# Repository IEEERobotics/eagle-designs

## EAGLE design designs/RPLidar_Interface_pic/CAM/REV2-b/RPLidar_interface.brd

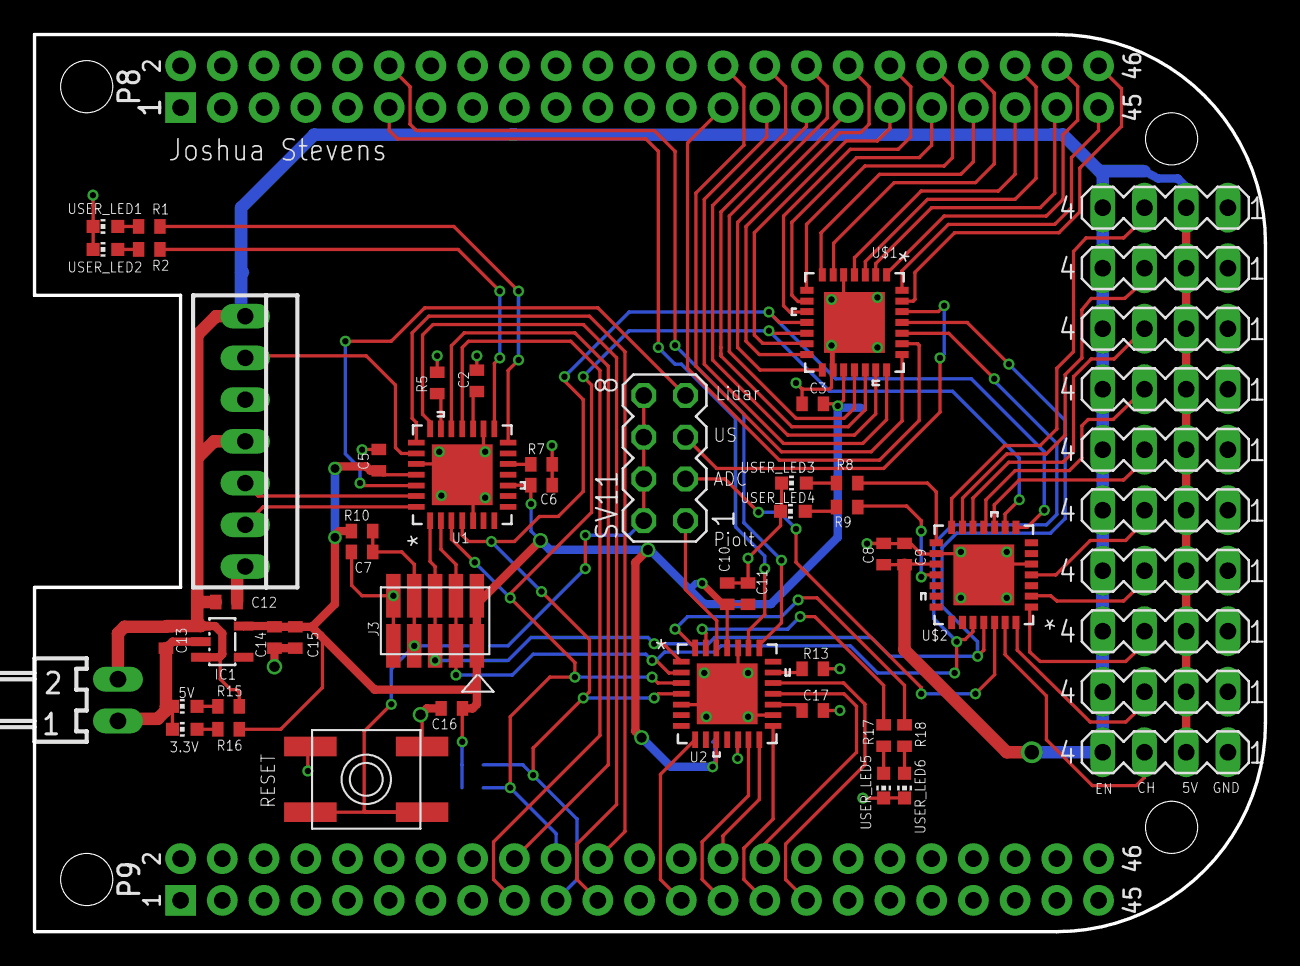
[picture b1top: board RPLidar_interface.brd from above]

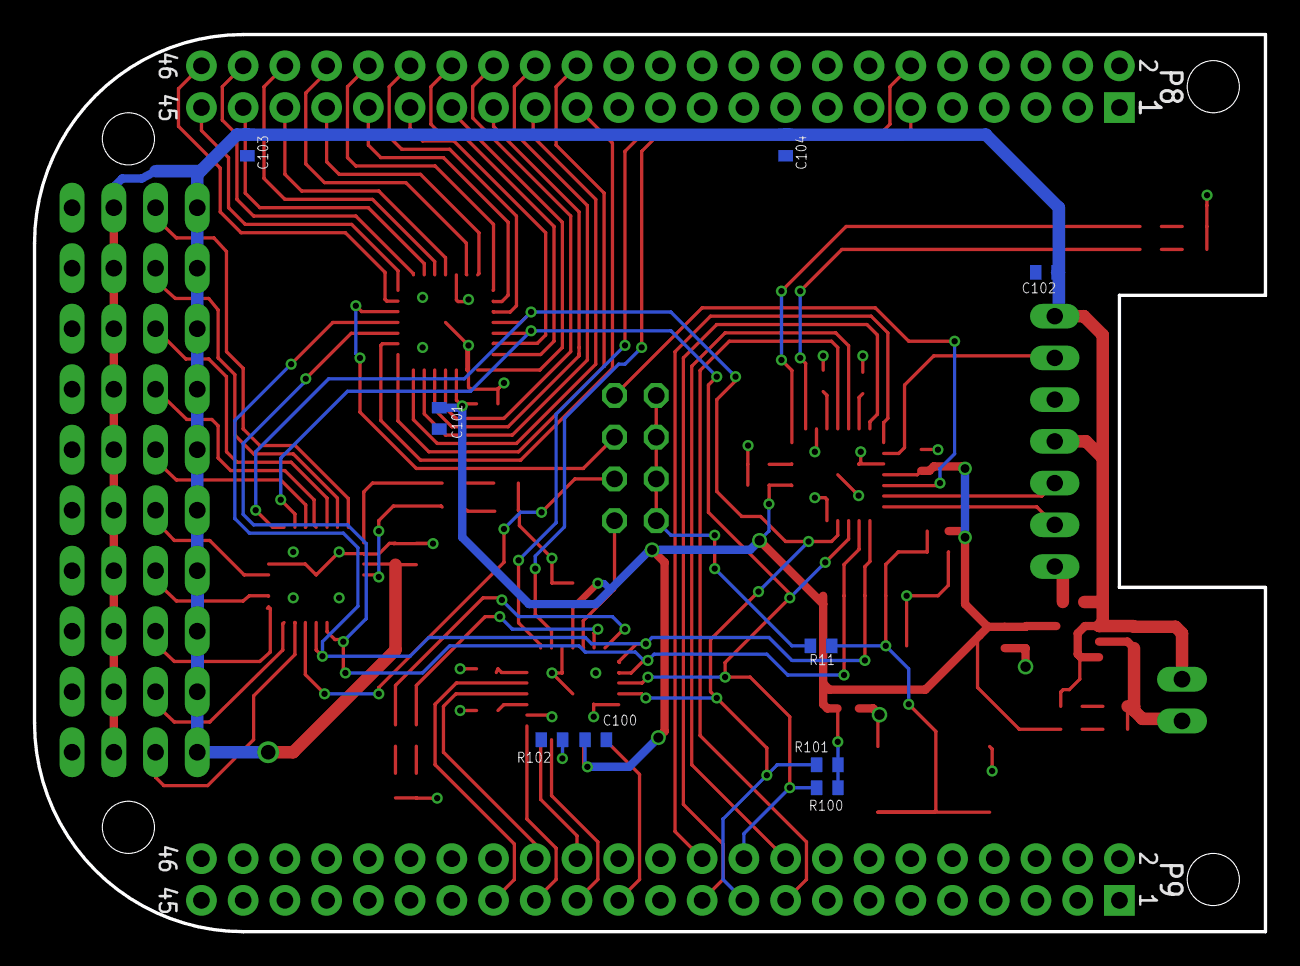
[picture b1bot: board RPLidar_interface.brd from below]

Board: 2 copper layers, 74.9 x 54.6 mm, 65 parts (9 on the bottom side), 78 nets.

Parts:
3.3V, 5V: CHIP-LED0603
C2, C7, C17: .1uF; C0402
C3, C6, C9, C10, C15, C100, C101: 0.1uF; C0402
C5, C8, C14: 1uF; C0402
C11, C16: .01uF; C0402
C12, C102, C103, C104: 5uF; C0402
C13: 10uF; C0402
IC1: TS5205; SOT25
J3: PIN-CONNECTOR74089; 10-PIN-SMD
J4: 22-05-7028-02; 7395-02
R1: 300; R0402
R2, R17, R18: 330; R0402
R5, R7, R13, R100, R101, R102: 0; R0402
R8, R9: 500; R0402
R10: 10k; R0402
R11: 100; R0402
R15, R16: 1K; R0402
RESET: EVQQ2; EVQ-Q2
SV1, SV2, SV3, SV4, SV5, SV6, SV7, SV8, SV9, SV10: MA04-1
SV11: MA04-2
U1, U2: PIC24FJ32GB002-I/ML; QFN65P600X600X100-29N
U$1, U$2: PIC16F73-I/ML; QFN65P600X600X100-28N
U$3: BEAGLE_BONE_BLACK_CAPE
USER_LED1, USER_LED2, USER_LED3, USER_LED4, USER_LED5, USER_LED6: CHIP-LED0603
X1: 22-23-2071

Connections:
5V: C8.1, C9.1, C12.1, C13.1, C102.1, C103.1, C104.1, IC1.1, IC1.3, J4.2, R15.2, SV1.2, SV1.4, SV2.2, SV2.4, SV3.2, SV3.4, SV4.2, SV4.4, SV5.2, SV5.4, SV6.2, SV6.4, SV7.2, SV7.4, SV8.2, SV8.4, SV9.2, SV9.4, SV10.2, SV10.4, U$2.17, X1.1, X1.4
!SS: U1.18, U$3.P9.17
+3V3: C3.1, C5.1, C6.1, C10.1, C11.1, C14.1, C15.1, C16.1, C100.1, C101.1, IC1.5, J3.1, J3.2, R10.2, R16.2, R100.1, R101.1, U1.10, U1.25, U2.10, U2.25, U$1.17
CH1: SV10.3, U$2.27
CH2: SV9.3, U$2.28
CH3: SV8.3, U$2.1
CH4: SV7.3, U$2.2
CH5: SV6.3, U$2.4
CH6: SV5.3, U$2.10
CH7: SV4.3, U$2.11
CH8: SV3.3, U$2.12
CH9: SV2.3, U$2.13
CH10: SV1.3, U$2.14
GND: 3.3V.C, 5V.C, C2.2, C3.2, C5.2, C6.2, C7.2, C8.2, C9.2, C10.2, C11.2, C12.2, C13.2, C14.2, C15.2, C16.2, C17.2, C100.2, C101.2, C102.2, C103.2, C104.2, IC1.2, J3.9, J3.10, J4.1, R5.2, R7.2, R13.2, R102.2, RESET.A, RESET.A', SV1.1, SV2.1, SV3.1, SV4.1, SV5.1, SV6.1, SV7.1, SV8.1, SV9.1, SV10.1, U1.5, U1.16, U1.24, U1.29, U2.5, U2.16, U2.24, U2.29, U$1.5, U$1.16, U$1.29, U$2.5, U$2.16, U$2.29, U$3.P8.1, U$3.P8.2, U$3.P9.1, U$3.P9.2, USER_LED1.C, USER_LED2.C, USER_LED3.C, USER_LED4.C, USER_LED5.C, USER_LED6.C, X1.3, X1.7
ICSPCLK: J3.3, J3.4, U1.2, U2.2, U$1.24, U$2.24
ICSPDAT: J3.5, J3.6, U1.1, U2.1, U$1.25, U$2.25
MCLR/VPP_A: SV11.3, U$2.26
MCLR/VPP_P: SV11.1, U2.26
MCLR/VPP_U: SV11.5, U$1.26
MCLR_LIDAR: C7.1, J3.7, J3.8, R10.1, R11.2, RESET.B, RESET.B'
MISO: U1.21, U$3.P9.21
MOSI: U1.19, U$3.P9.18
unnamed: 3.3V.A, R16.1
unnamed: R1.1, USER_LED1.A
unnamed: R2.1, USER_LED2.A
unnamed: 5V.A, R15.1
unnamed: R17.1, USER_LED5.A
unnamed: R18.1, USER_LED6.A
unnamed: R8.1, USER_LED3.A
unnamed: R9.1, USER_LED4.A
unnamed: R11.1, SV11.2, SV11.4, SV11.6, SV11.8
P8.11: U2.23, U$3.P8.11
P8.12: U2.22, U$3.P8.12
P8.27: U$1.23, U$3.P8.27
P8.28: U$1.22, U$3.P8.28
P8.29: U$1.21, U$3.P8.29
P8.30: U$1.20, U$3.P8.30
P8.31: U$1.19, U$3.P8.31
P8.32: U$1.18, U$3.P8.32
P8.33: U$1.15, U$3.P8.33
P8.34: U$1.14, U$3.P8.34
P8.35: U$1.13, U$3.P8.35
P8.36: U$1.10, U$3.P8.36
P8.37: U$1.9, U$3.P8.37
P8.38: U$1.8, U$3.P8.38
P8.39: U$1.7, U$3.P8.39
P8.40: U$1.6, U$3.P8.40
P8.41: U$1.4, U$3.P8.41
P8.42: U$1.3, U$3.P8.42
P8.43: U$1.2, U$3.P8.43
P8.44: U$1.1, U$3.P8.44
P8.45: U$1.28, U$3.P8.45
P8.46: U$1.27, U$3.P8.46
P9.25: U2.8, U$3.P9.25
P9.27: U2.13, U$3.P9.27
P9.28: U2.14, U$3.P9.28
P9.29: U2.15, U$3.P9.29
P9.30: U2.18, U$3.P9.30
P9.31: U2.19, U$3.P9.31
RPLIDAR_EN: U1.23, X1.2
SCL: R101.2, U1.4, U2.4, U$1.11, U$2.8, U$3.P9.19
SCLK: U1.22, U$3.P9.22
SDA: R100.2, U1.3, U2.3, U$1.12, U$2.9, U$3.P9.20
UART_RX: U1.27, X1.5
UART_TX: U1.28, X1.6
USER1: R1.2, U1.14
USER2: R2.2, U1.15
USER3: R18.2, U2.28
USER4: R17.2, U2.27
USER5: R8.2, U$2.15
USER6: R9.2, U$2.18
VBUS: R7.1, U1.12
VBUS_P: R102.1, U2.12
VDDCORE: C2.1, U1.17
VDDCORE_P: C17.1, U2.17
VPP/MCLR: SV11.7, U1.26
VUSB: R5.1, U1.20
VUSB_P: R13.1, U2.20

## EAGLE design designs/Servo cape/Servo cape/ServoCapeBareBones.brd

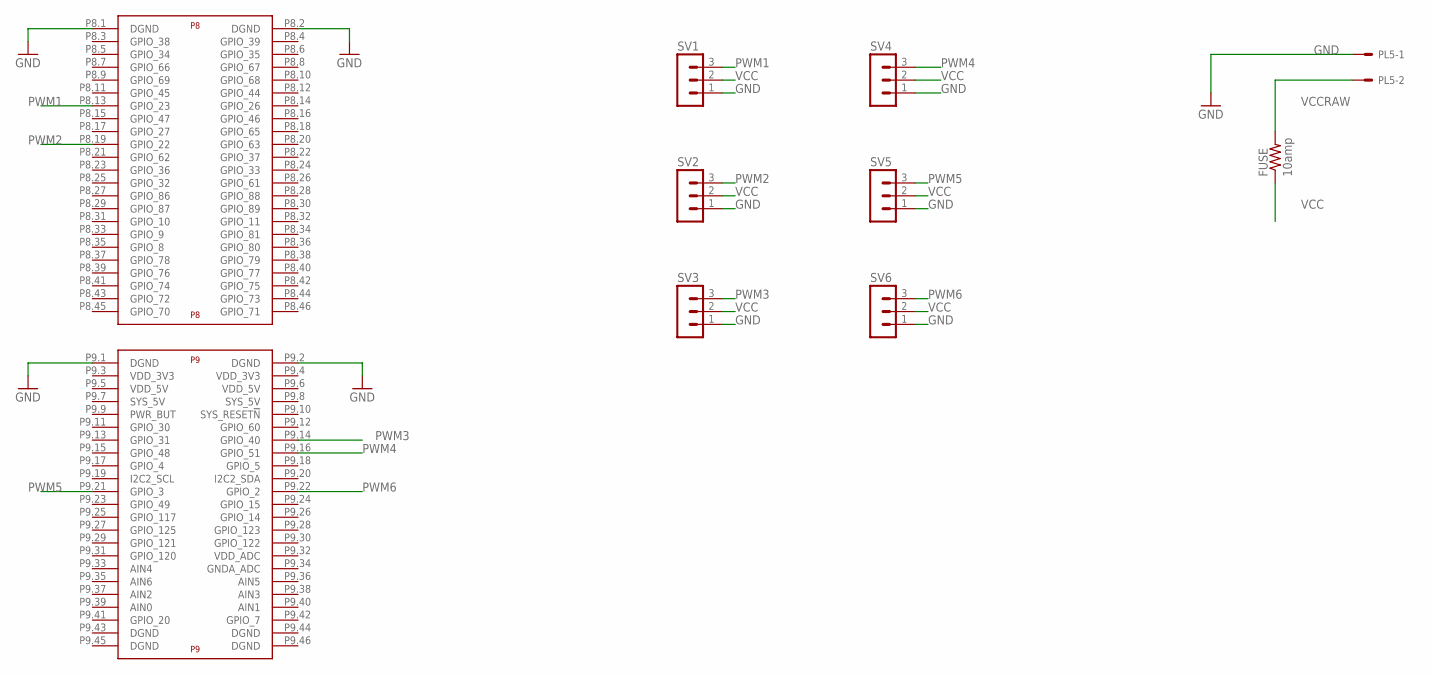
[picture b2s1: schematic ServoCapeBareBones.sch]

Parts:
FUSE: 10amp; R1206
PL5: 555X-2H; 5569-2
SV1, SV2, SV3, SV4, SV5, SV6: MA03-1
U$1: BEAGLE_BONE_BLACK_CAPE

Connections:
GND: PL5.1, SV1.1, SV2.1, SV3.1, SV4.1, SV5.1, SV6.1, U$1.P8.1 (DGND), U$1.P8.2 (DGND), U$1.P9.1 (DGND), U$1.P9.2 (DGND)
PWM1: SV1.3, U$1.P8.13 (GPIO_23)
PWM2: SV2.3, U$1.P8.19 (GPIO_22)
PWM3: SV3.3, U$1.P9.14 (GPIO_40)
PWM4: SV4.3, U$1.P9.16 (GPIO_51)
PWM5: SV5.3, U$1.P9.21 (GPIO_3)
PWM6: SV6.3, U$1.P9.22 (GPIO_2)
VCC: FUSE.1, SV1.2, SV2.2, SV3.2, SV4.2, SV5.2, SV6.2
VCCRAW: FUSE.2, PL5.2

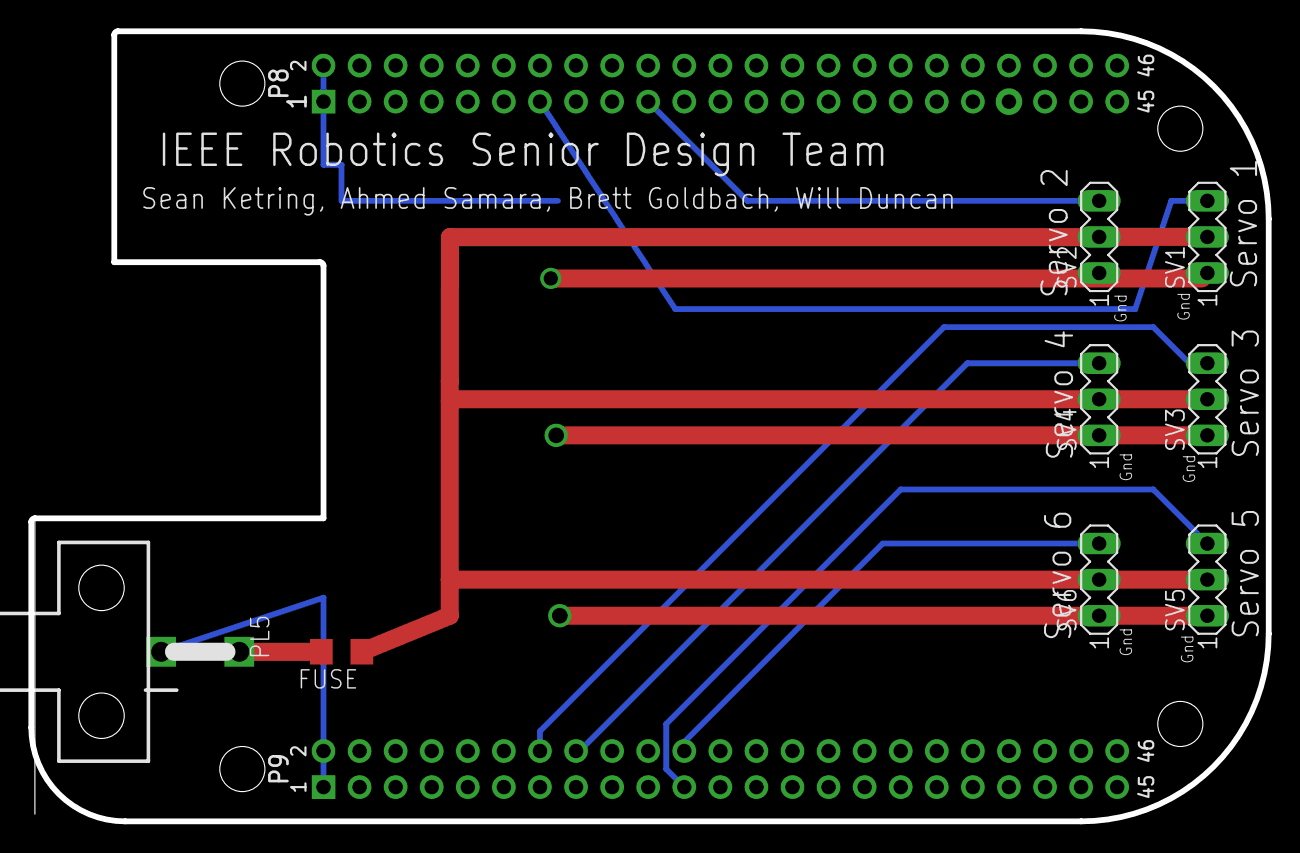
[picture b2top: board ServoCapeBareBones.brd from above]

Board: 2 copper layers, 87.1 x 55.6 mm, 9 parts (0 on the bottom side), 9 nets.

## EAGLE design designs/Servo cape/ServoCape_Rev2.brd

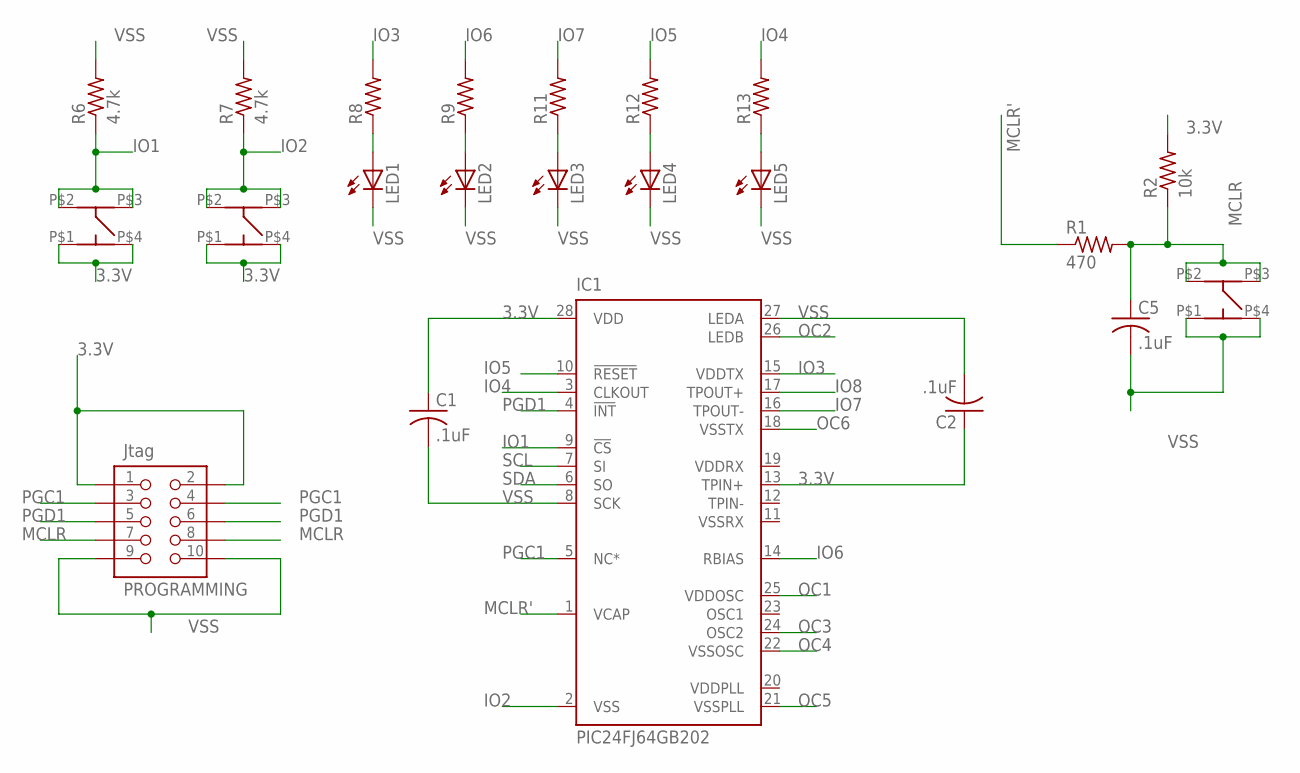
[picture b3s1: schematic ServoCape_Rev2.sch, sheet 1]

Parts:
C1, C2, C5: .1uF; C0805
IC1: PIC24FJ64GB202; DIL28-3
LED1, LED2, LED3, LED4, LED5: LED_LEDCHIPLED_1206; LED_CHIPLED_1206
PROGRAMMING: Jtag; MOTHER-BOARD-REV5_10-PIN-SMD
R1: 470; R0805
R2: 10k; R0805
R6, R7: 4.7k; R0805
R8, R9, R11, R12, R13: R-US_M0805; M0805
U$1: Switch3; MC32882_FINAL
U$4: Switch1; MC32882_FINAL
U$5: Switch2; MC32882_FINAL

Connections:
3.3V: C1.1, C2.1, IC1.13 (TPIN+), IC1.28 (VDD), PROGRAMMING.1, PROGRAMMING.2, R2.2, U$4.P$1 (P1), U$4.P$4 (P4), U$5.P$1 (P1), U$5.P$4 (P4); also elsewhere on the board
IO1: IC1.9 (!CS), R6.1, U$4.P$2 (P2), U$4.P$3 (P3)
IO2: IC1.2 (VSS), R7.1, U$5.P$2 (P2), U$5.P$3 (P3)
IO3: IC1.15 (VDDTX), R8.2
IO4: IC1.3 (CLKOUT), R13.2
IO5: IC1.10 (!RESET), R12.2
IO6: IC1.14 (RBIAS), R9.2
IO7: IC1.16 (TPOUT-), R11.2
IO8: IC1.17 (TPOUT+)
MCLR: C5.1, PROGRAMMING.7, PROGRAMMING.8, R1.2, R2.1, U$1.P$2 (P2), U$1.P$3 (P3)
MCLR': IC1.1 (VCAP), R1.1
unnamed: LED1.A, R8.1
unnamed: LED2.A, R9.1
unnamed: LED3.A, R11.1
unnamed: LED4.A, R12.1
unnamed: LED5.A, R13.1
OC1: IC1.25 (VDDOSC); also elsewhere on the board
OC2: IC1.26 (LEDB); also elsewhere on the board
OC3: IC1.24 (OSC2); also elsewhere on the board
OC4: IC1.22 (VSSOSC); also elsewhere on the board
OC5: IC1.21 (VSSPLL); also elsewhere on the board
OC6: IC1.18 (VSSTX); also elsewhere on the board
PGC1: IC1.5 (NC*), PROGRAMMING.3, PROGRAMMING.4
PGD1: IC1.4 (!INT), PROGRAMMING.5, PROGRAMMING.6
SCL: IC1.7 (SI); also elsewhere on the board
SDA: IC1.6 (SO); also elsewhere on the board
VSS: C1.2, C2.2, C5.2, IC1.8 (SCK), IC1.27 (LEDA), LED1.C, LED2.C, LED3.C, LED4.C, LED5.C, PROGRAMMING.9, PROGRAMMING.10, R6.2, R7.2, U$1.P$1 (P1), U$1.P$4 (P4); also elsewhere on the board

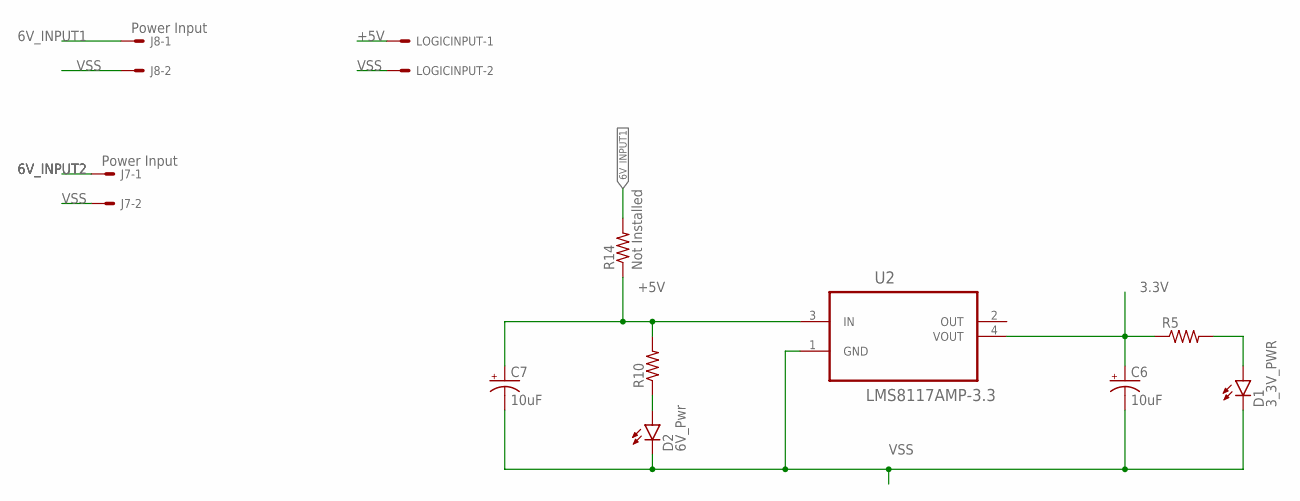
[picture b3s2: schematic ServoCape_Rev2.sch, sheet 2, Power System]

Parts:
C6, C7: 10uF; EIA3216
D1: 3_3V_PWR; FKIT-LED-1206
D2: 6V_Pwr; FKIT-LED-1206
J7, J8: Power Input; 7395-02
LOGICINPUT: 22-05-7028-02; 7395-02
R5, R10: R-US_R0805W; R0805W
R14: Not Installed; R0402
U2: LMS8117AMP-3.3; SOT230P696X180-4N

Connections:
3.3V: C6.A (+), R5.1, U2.4 (VOUT); also elsewhere on the board
6V_INPUT1: J8.1, R14.2; also elsewhere on the board
6V_INPUT2: J7.1; also elsewhere on the board
+5V: C7.A (+), LOGICINPUT.1, R10.2, R14.1, U2.3 (IN)
unnamed: D1.A, R5.2
unnamed: D2.A, R10.1
VSS: C6.C (-), C7.C (-), D1.C, D2.C, J7.2, J8.2, LOGICINPUT.2, U2.1 (GND); also elsewhere on the board

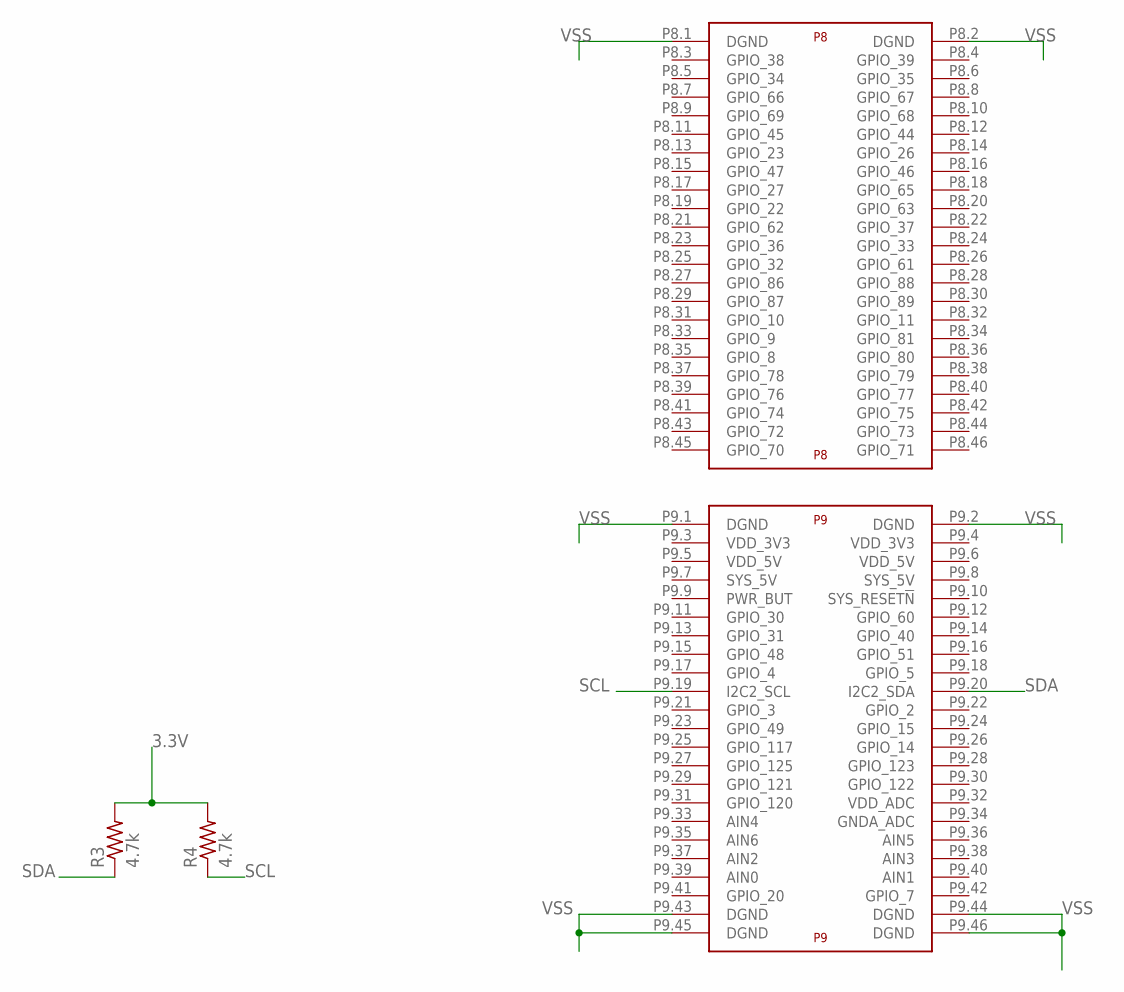
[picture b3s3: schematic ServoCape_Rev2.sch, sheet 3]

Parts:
R3, R4: 4.7k; R0805
U$2: BEAGLE_BONE_BLACK_CAPE

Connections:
3.3V: R3.2, R4.2; also elsewhere on the board
SCL: R4.1, U$2.P9.19 (I2C2_SCL); also elsewhere on the board
SDA: R3.1, U$2.P9.20 (I2C2_SDA); also elsewhere on the board
VSS: U$2.P8.1 (DGND), U$2.P8.2 (DGND), U$2.P9.1 (DGND), U$2.P9.2 (DGND), U$2.P9.43 (DGND), U$2.P9.44 (DGND), U$2.P9.45 (DGND), U$2.P9.46 (DGND); also elsewhere on the board

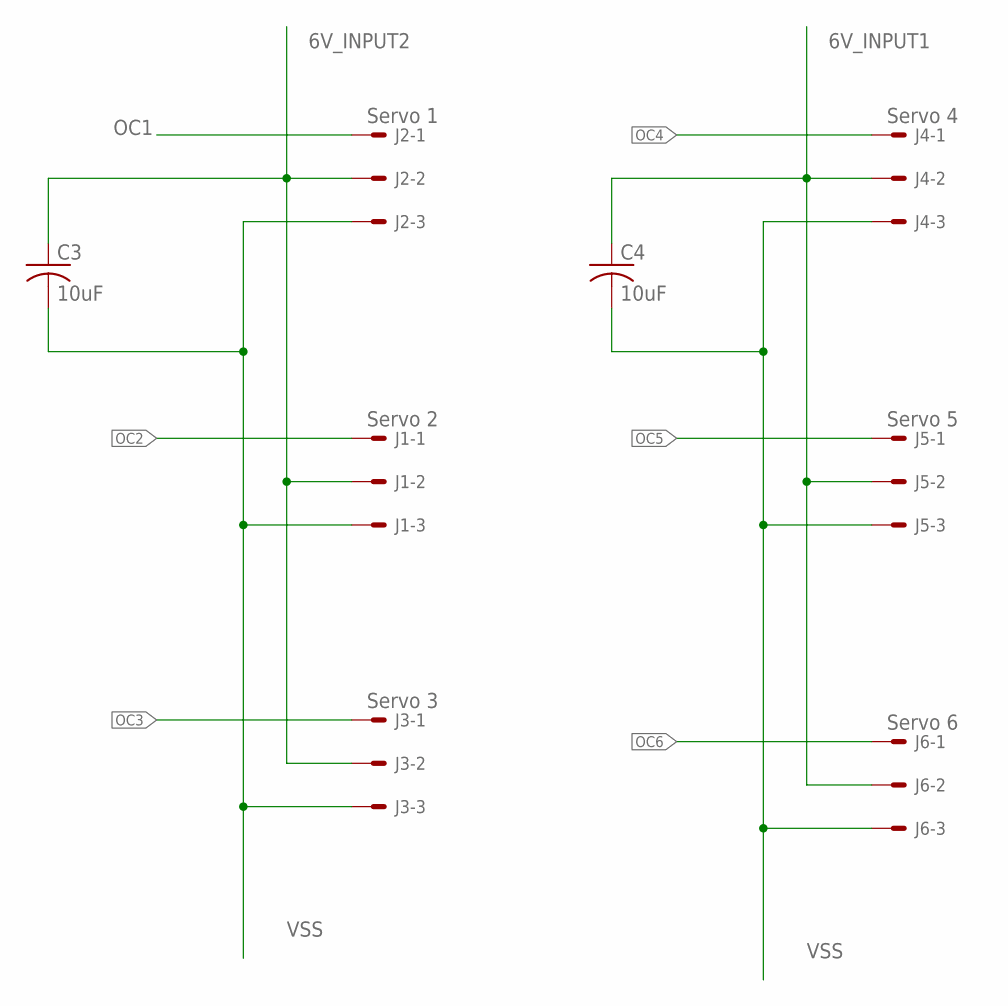
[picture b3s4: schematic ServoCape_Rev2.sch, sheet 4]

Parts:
C3, C4: 10uF; C0805
J1: Servo 2; 7395-03
J2: Servo 1; 7395-03
J3: Servo 3; 7395-03
J4: Servo 4; 7395-03
J5: Servo 5; 7395-03
J6: Servo 6; 7395-03

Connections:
6V_INPUT1: C4.1, J4.2, J5.2, J6.2; also elsewhere on the board
6V_INPUT2: C3.1, J1.2, J2.2, J3.2; also elsewhere on the board
OC1: J2.1; also elsewhere on the board
OC2: J1.1; also elsewhere on the board
OC3: J3.1; also elsewhere on the board
OC4: J4.1; also elsewhere on the board
OC5: J5.1; also elsewhere on the board
OC6: J6.1; also elsewhere on the board
VSS: C3.2, C4.2, J1.3, J2.3, J3.3, J4.3, J5.3, J6.3; also elsewhere on the board

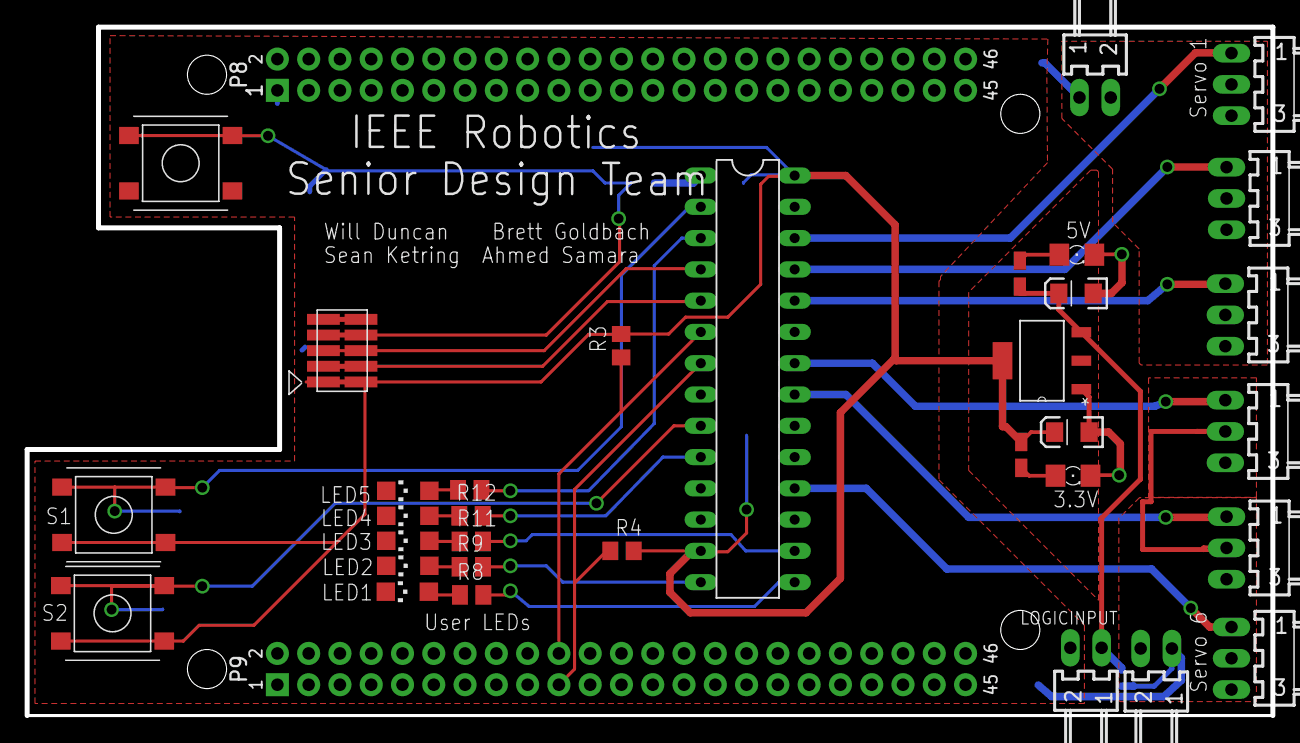
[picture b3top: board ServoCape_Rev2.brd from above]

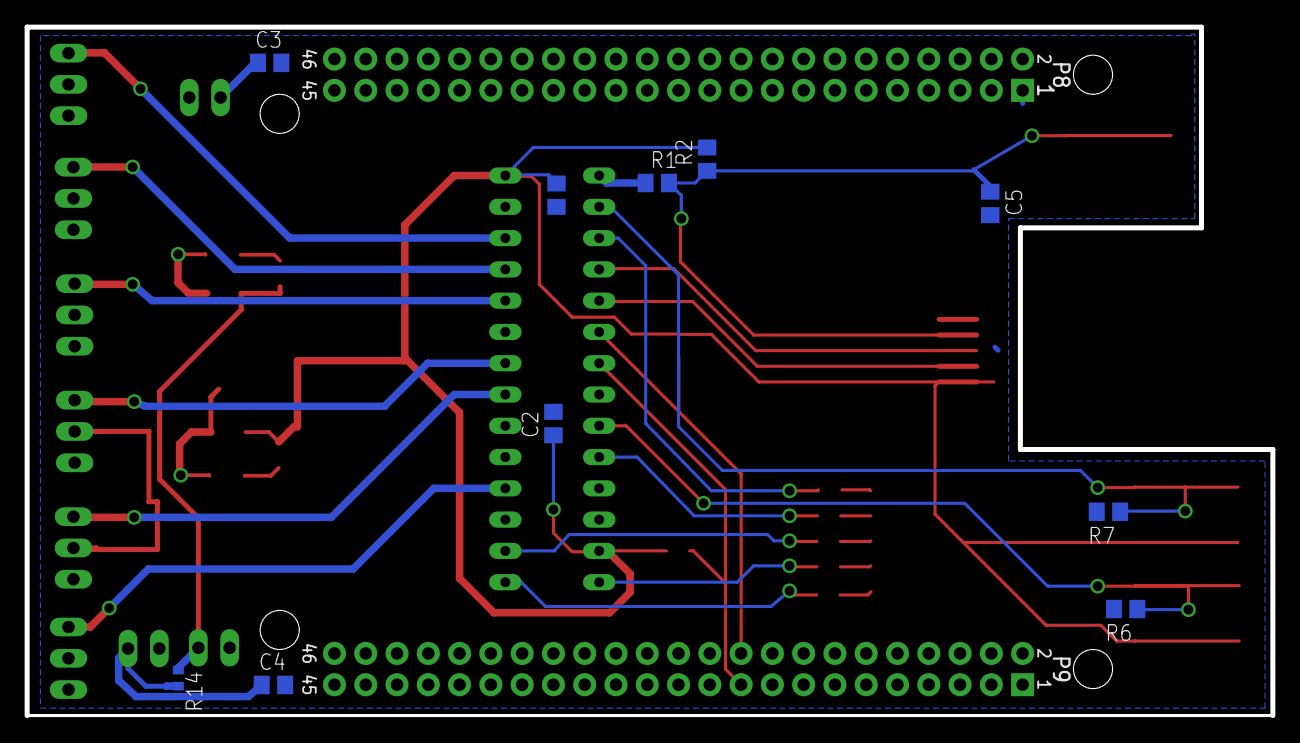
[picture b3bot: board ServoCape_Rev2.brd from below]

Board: 2 copper layers, 101.2 x 55.9 mm, 44 parts (10 on the bottom side), 31 nets.

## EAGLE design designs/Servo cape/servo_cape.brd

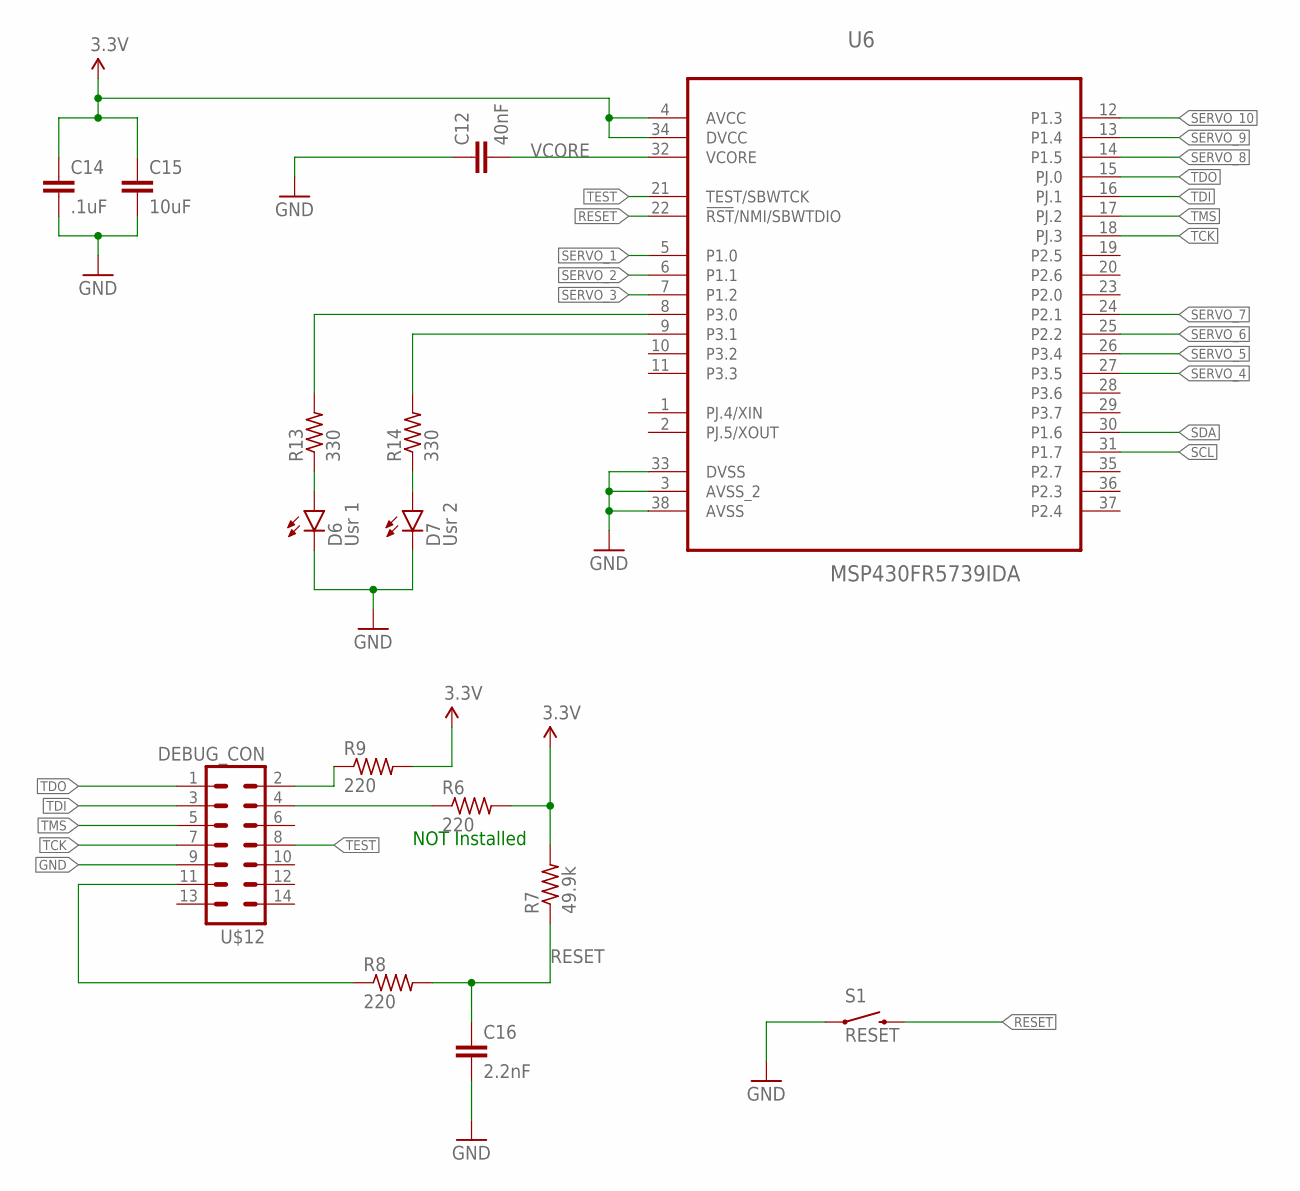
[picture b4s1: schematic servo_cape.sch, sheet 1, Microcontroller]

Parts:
C12: 40nF; 0805
C14: .1uF; 0805
C15: 10uF; 0805
C16: 2.2nF; 0805
D6: Usr 1; FKIT-LED-1206
D7: Usr 2; FKIT-LED-1206
R6, R8, R9: 220; R0805W
R7: 49.9k; R0805W
R13, R14: 330; R0805W
S1: RESET; TACTILE_SWITCH_TALL
U6: MSP430FR5739IDA; SOP65P810X120-38N
U$12: DEBUG_CON; DEBUG_SM

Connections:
3.3V: C14.1, C15.1, R6.2, R7.2, R9.2, U6.4 (AVCC), U6.34 (DVCC); also elsewhere on the board
GND: C12.1, C14.2, C15.2, C16.2, D6.C, D7.C, S1.A2 (1), U6.3 (AVSS_2), U6.33 (DVSS), U6.38 (AVSS), U$12.9; also elsewhere on the board
unnamed: R14.2, U6.9 (P3.1)
unnamed: R6.1, U$12.4
unnamed: D6.A, R13.1
unnamed: D7.A, R14.1
unnamed: R8.1, U$12.11
unnamed: R9.1, U$12.2
unnamed: R13.2, U6.8 (P3.0)
RESET: C16.1, R7.1, R8.2, S1.B2 (2), U6.22 (!RST!/NMI/SBWTDIO)
SCL: U6.31 (P1.7); also elsewhere on the board
SDA: U6.30 (P1.6); also elsewhere on the board
SERVO_1: U6.5 (P1.0); also elsewhere on the board
SERVO_2: U6.6 (P1.1); also elsewhere on the board
SERVO_3: U6.7 (P1.2); also elsewhere on the board
SERVO_4: U6.27 (P3.5); also elsewhere on the board
SERVO_5: U6.26 (P3.4); also elsewhere on the board
SERVO_6: U6.25 (P2.2); also elsewhere on the board
SERVO_7: U6.24 (P2.1); also elsewhere on the board
SERVO_8: U6.14 (P1.5)
SERVO_9: U6.13 (P1.4)
SERVO_10: U6.12 (P1.3)
TCK: U6.18 (PJ.3), U$12.7
TDI: U6.16 (PJ.1), U$12.3
TDO: U6.15 (PJ.0), U$12.1
TEST: U6.21 (TEST/SBWTCK), U$12.8
TMS: U6.17 (PJ.2), U$12.5
VCORE: C12.2, U6.32 (VCORE)

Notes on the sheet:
NOT Installed

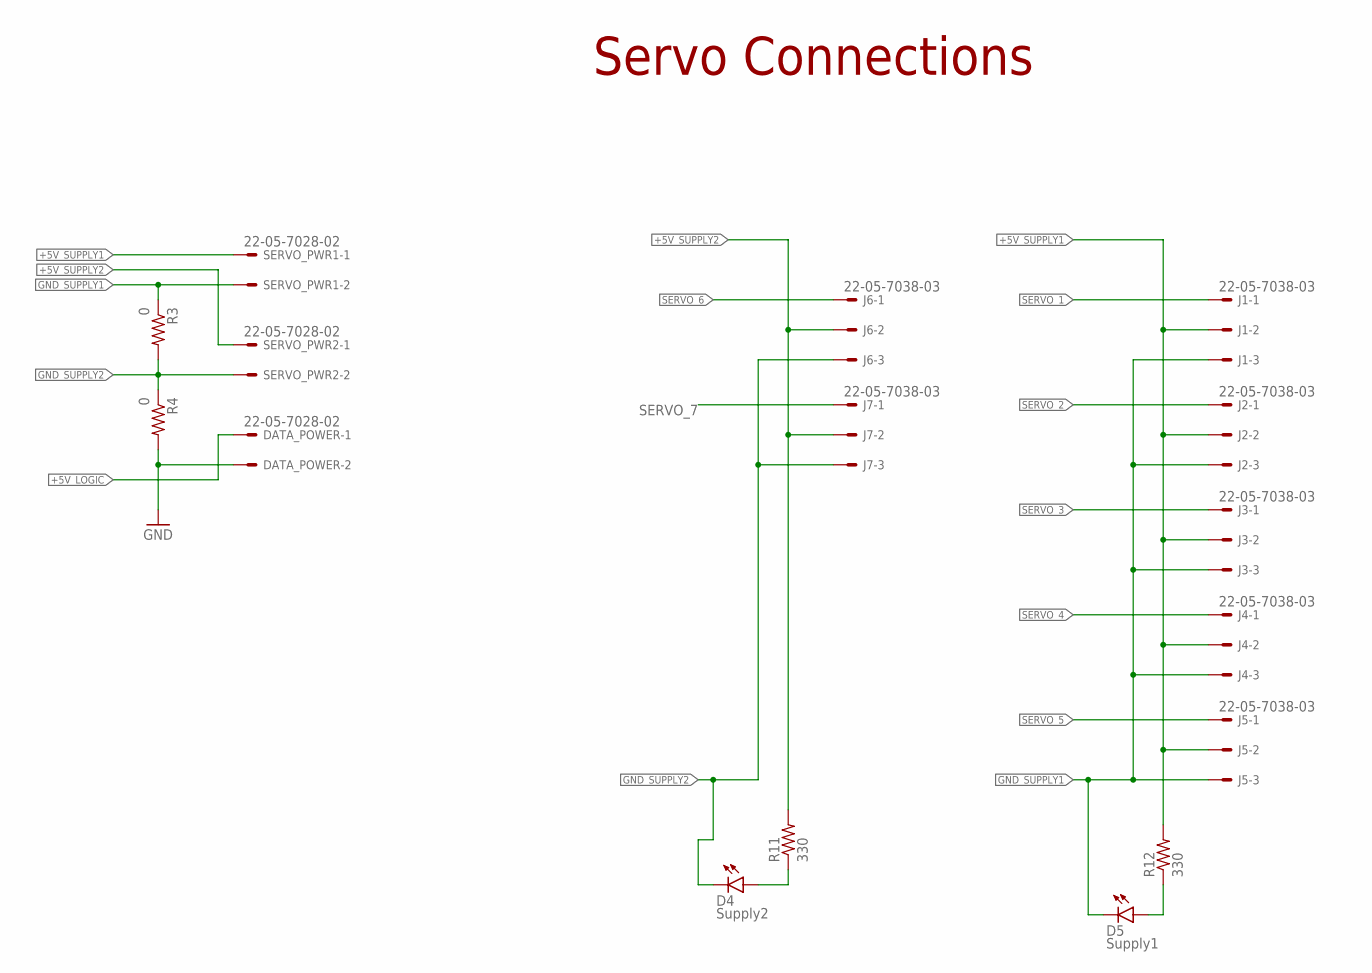
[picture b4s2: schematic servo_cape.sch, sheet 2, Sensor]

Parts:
D4: Supply2; FKIT-LED-1206
D5: Supply1; FKIT-LED-1206
DATA_POWER: 22-05-7028-02; 7395-02
J1, J2, J3, J4, J5, J6, J7: 22-05-7038-03; 7395-03
R3, R4: 0; R0805W
R11, R12: 330; R0805W
SERVO_PWR1, SERVO_PWR2: 22-05-7028-02; 7395-02

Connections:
+5V_LOGIC: DATA_POWER.1; also elsewhere on the board
+5V_SUPPLY1: J1.2, J2.2, J3.2, J4.2, J5.2, R12.2, SERVO_PWR1.1
+5V_SUPPLY2: J6.2, J7.2, R11.2, SERVO_PWR2.1
GND: DATA_POWER.2, R4.2; also elsewhere on the board
GND_SUPPLY1: D5.C, J1.3, J2.3, J3.3, J4.3, J5.3, R3.1, SERVO_PWR1.2
GND_SUPPLY2: D4.C, J6.3, J7.3, R3.2, R4.1, SERVO_PWR2.2
unnamed: D5.A, R12.1
unnamed: D4.A, R11.1
SERVO_1: J1.1; also elsewhere on the board
SERVO_2: J2.1; also elsewhere on the board
SERVO_3: J3.1; also elsewhere on the board
SERVO_4: J4.1; also elsewhere on the board
SERVO_5: J5.1; also elsewhere on the board
SERVO_6: J6.1; also elsewhere on the board
SERVO_7: J7.1; also elsewhere on the board

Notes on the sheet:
Servo Connections

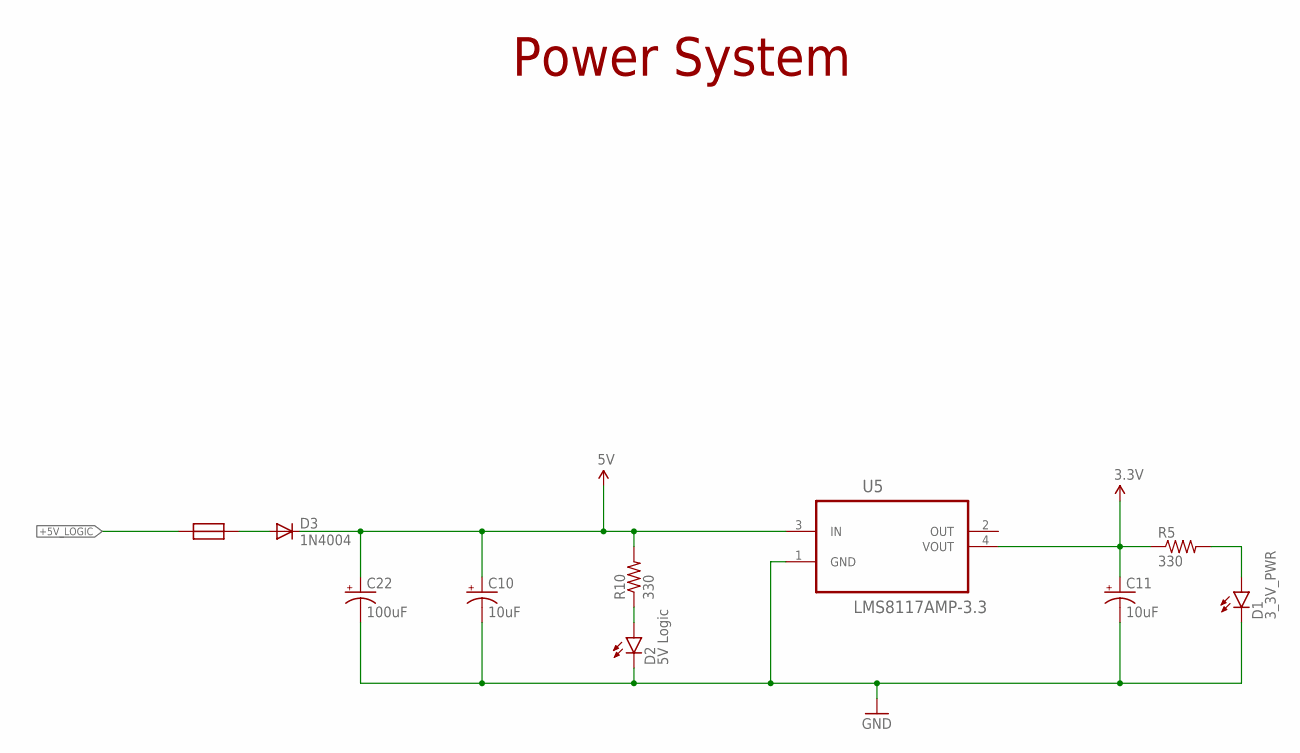
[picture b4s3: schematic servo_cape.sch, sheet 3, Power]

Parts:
C10, C11: 10uF; EIA3216
C22: 100uF; EIA7343
D1: 3_3V_PWR; FKIT-LED-1206
D2: 5V Logic; FKIT-LED-1206
D3: 1N4004; DO41-10
R5, R10: 330; R0805W
U5: LMS8117AMP-3.3; SOT230P696X180-4N
U$3: NANO_FUSE

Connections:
3.3V: C11.A (+), R5.1, U5.4 (VOUT); also elsewhere on the board
5V: C10.A (+), C22.A (+), D3.C, R10.2, U5.3 (IN)
+5V_LOGIC: U$3.1; also elsewhere on the board
GND: C10.C (-), C11.C (-), C22.C (-), D1.C, D2.C, U5.1 (GND); also elsewhere on the board
unnamed: D1.A, R5.2
unnamed: D2.A, R10.1
unnamed: D3.A, U$3.2

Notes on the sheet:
Power System

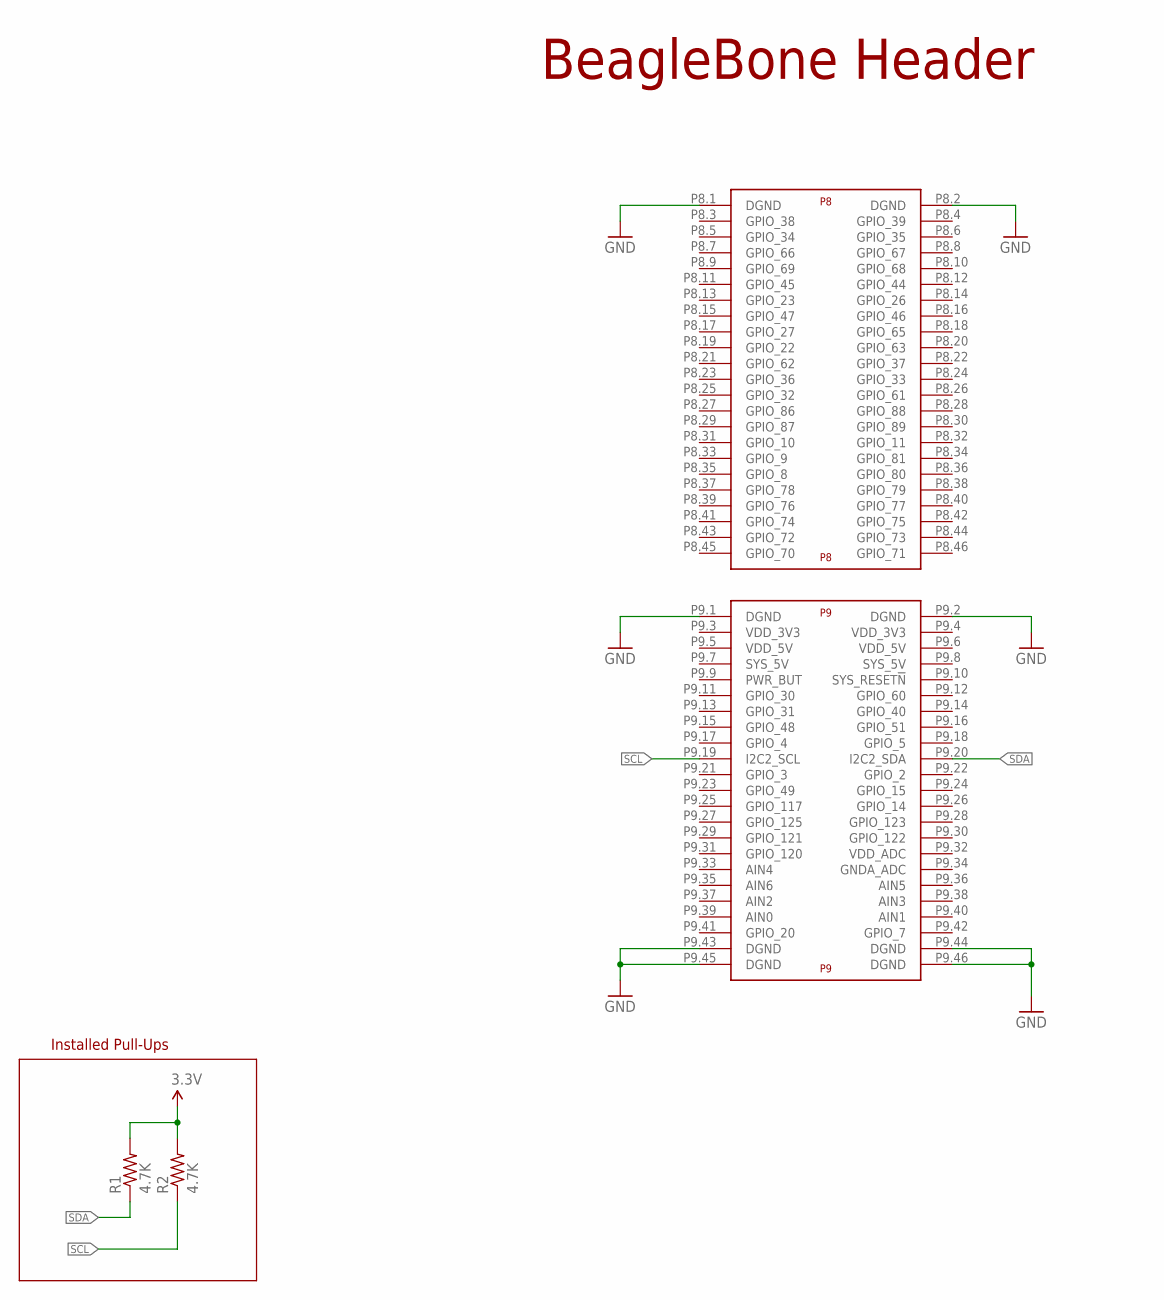
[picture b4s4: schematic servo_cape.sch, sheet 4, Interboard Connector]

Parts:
R1, R2: 4.7K; R0805W
U$1: BEAGLE_BONE_BLACK_CAPE

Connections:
3.3V: R1.2, R2.2; also elsewhere on the board
GND: U$1.P8.1 (DGND), U$1.P8.2 (DGND), U$1.P9.1 (DGND), U$1.P9.2 (DGND), U$1.P9.43 (DGND), U$1.P9.44 (DGND), U$1.P9.45 (DGND), U$1.P9.46 (DGND); also elsewhere on the board
SCL: R2.1, U$1.P9.19 (I2C2_SCL); also elsewhere on the board
SDA: R1.1, U$1.P9.20 (I2C2_SDA); also elsewhere on the board

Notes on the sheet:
BeagleBone Header
Installed Pull-Ups

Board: 2 copper layers, 44 parts (0 on the bottom side), 36 nets, no tracks yet.

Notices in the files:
parts and their libraries:
SparkFun-Boards: Licensing: Creative Commons ShareAlike 4.0 International - https://creativecommons.org/licenses/by-sa/4.0
